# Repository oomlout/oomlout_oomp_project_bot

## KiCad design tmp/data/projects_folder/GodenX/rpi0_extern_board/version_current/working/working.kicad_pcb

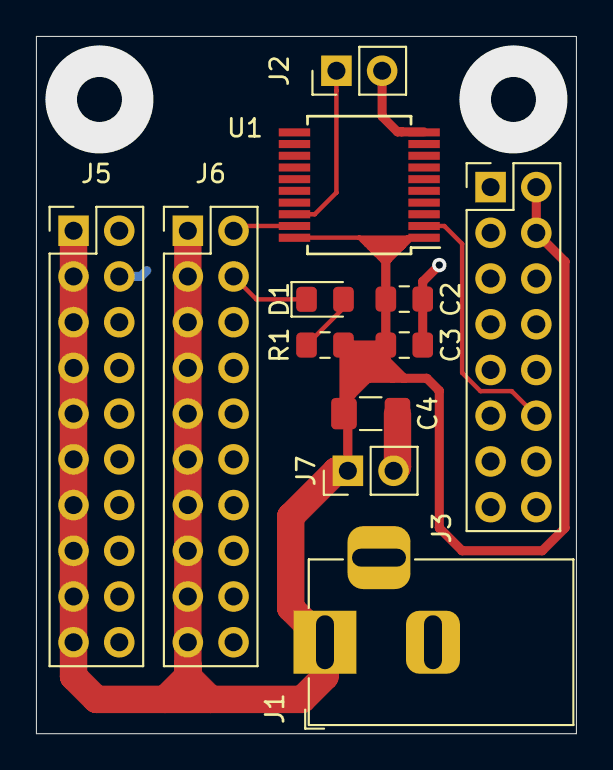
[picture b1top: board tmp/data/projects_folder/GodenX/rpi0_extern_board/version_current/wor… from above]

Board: 2 copper layers, 30.0 x 38.7 mm, 12 parts (0 on the bottom side), 5 nets.

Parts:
C2: 10uF; C_0805_2012Metric_Pad1.15x1.40mm_HandSolder
C3: 0.1uF; C_0805_2012Metric_Pad1.15x1.40mm_HandSolder
C4: 47uF; C_1206_3216Metric_Pad1.42x1.75mm_HandSolder
D1: LED; LED_0805_2012Metric_Pad1.15x1.40mm_HandSolder
J1: Conn_02x08_Odd_Even; PinHeader_2x08_P2.54mm_Vertical
J2, J7: Conn_01x02; PinHeader_1x02_P2.54mm_Vertical
J3: Jack-DC; BarrelJack_Horizontal
J5, J6: Conn_02x10_Odd_Even; PinHeader_2x10_P2.54mm_Vertical
R1: 10K; R_0805_2012Metric_Pad1.15x1.40mm_HandSolder
U1: 74HC245; SSOP-20_5.3x7.2mm_P0.65mm

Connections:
0: C2.2, C3.2, C4.2, D1.1, J1.6, J1.9, J1.14, J2.2, J3.2, J5.2, J5.4, J5.6, J5.8, J5.10, J5.12, J5.14, J5.16, J5.18, J5.20, J6.2, J6.4, J6.6, J6.8, J6.10, J6.12, J6.14, J6.16, J6.18, J6.20, J7.2, U1.10, U1.19
+5V: C2.1, C3.1, C4.1, J1.2, J1.4, J3.1, J5.1, J5.3, J5.5, J5.7, J5.9, J5.11, J5.13, J5.15, J5.17, J5.19, J6.1, J6.3, J6.5, J6.7, J6.9, J6.11, J6.13, J6.15, J6.17, J6.19, J7.1, R1.1, U1.1, U1.20
/Data: J1.12, U1.2
unnamed: D1.2, R1.2
unnamed: J2.1, U1.18

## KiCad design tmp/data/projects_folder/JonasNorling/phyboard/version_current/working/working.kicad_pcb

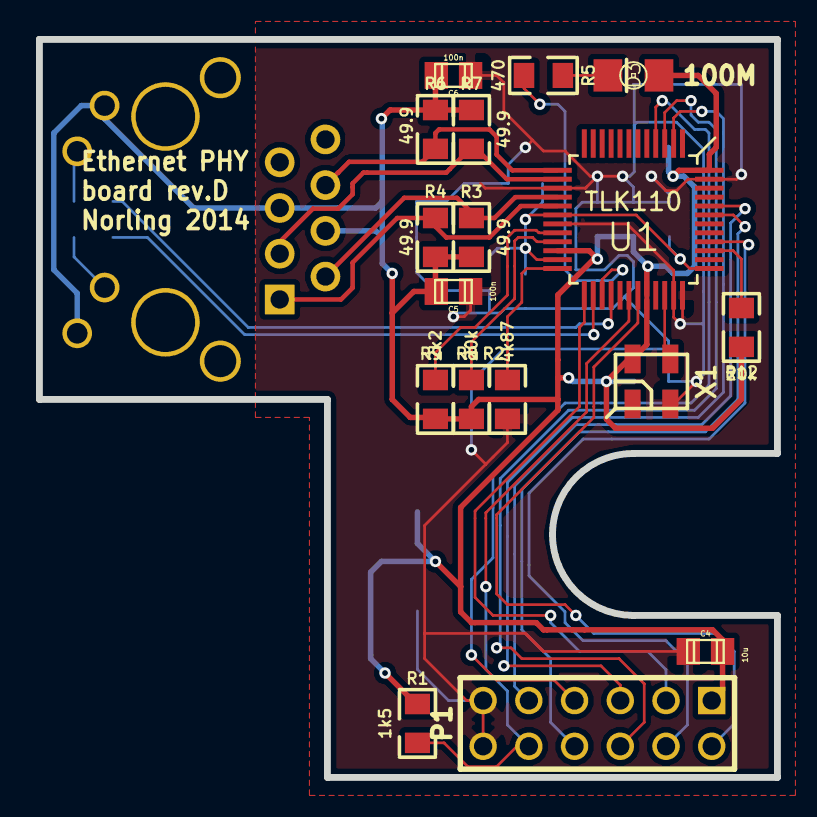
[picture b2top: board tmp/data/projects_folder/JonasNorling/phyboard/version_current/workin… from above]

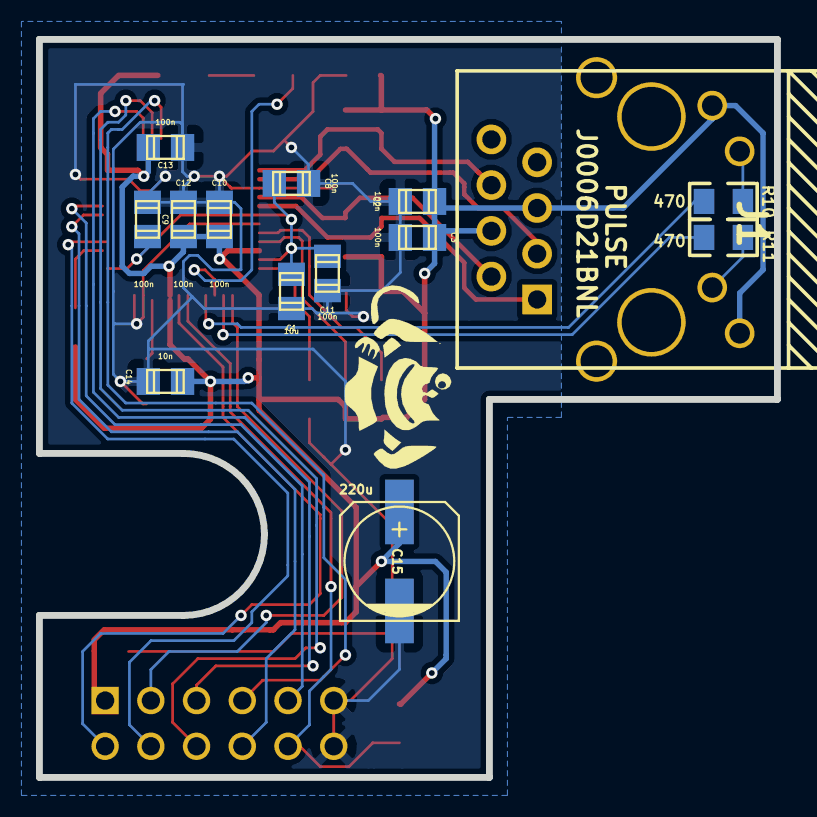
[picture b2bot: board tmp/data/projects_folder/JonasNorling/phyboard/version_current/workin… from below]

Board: 2 copper layers, 41.0 x 41.0 mm, 31 parts (14 on the bottom side), 27 nets.

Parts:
C1, C4: 10u; c_0805
C2, C3, C5, C6, C8, C9, C10, C11, C12, C13: 100n; c_0805
C14: 10n; c_0805
C15: 220u; c_elec_6.3x5.3
D3: LED; LED-1206
J1: PULSE-J0006; pulse-J0006D21BNL
P1: CONN_6X2; pin_array_6x2
R1: 1k5; SM0805-jonas
R2: 4k87; SM0805-jonas
R3, R4, R6, R7: 49.9; SM0805-jonas
R5, R10, R11: 470; SM0805-jonas
R8, R12: 20k; SM0805-jonas
R9: 2k2; SM0805-jonas
U1: TLK110; QFP50P900X900-48M
X1: ASEMB-50.000MHZ-LC-T; oscillator-3.2x2.5

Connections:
+3.3V: C2.1, C3.1, C4.1, C5.1, C6.1, C10.1, C12.1, C13.1, C14.1, C15.1, D3.1, J1.4, J1.5, J1.9, J1.12, P1.1, R1.2, R3.1, R4.2, R6.1, R7.2, R8.2, R9.2, R12.2, U1.22, U1.32, U1.48, X1.4
/ETH_CLK: P1.3, U1.25
/ETH_CRS: P1.4, U1.40
/ETH_MDC: P1.2, U1.31
/ETH_MDIO: P1.10, R1.1, U1.30
/ETH_RxD0: P1.8, U1.43
/ETH_RxD1: P1.9, U1.44
/ETH_TX_EN: P1.5, U1.2
/ETH_TxD0: P1.6, U1.3
/ETH_TxD1: P1.7, U1.4
/LED1: J1.11, R10.2
/LED2: J1.10, R11.2
/LED3: D3.2, R5.2
/OSC: U1.34, X1.3
/PFB: C1.1, C8.1, C9.1, C11.1, U1.18, U1.23, U1.37
/RD+: J1.3, R7.1, U1.14
/RD-: J1.6, R6.2, U1.13
/RMII_MODE: R12.1, U1.39
/TD+: J1.1, R4.1, U1.17
/TD-: J1.2, R3.2, U1.16
GND: C1.2, C2.2, C3.2, C4.2, C5.2, C6.2, C8.2, C9.2, C10.2, C11.2, C12.2, C13.2, C14.2, C15.2, P1.11, P1.12, R2.2, U1.15, U1.19, U1.35, U1.36, U1.47, X1.2
unnamed: R2.1, U1.24
unnamed: R8.1, U1.21
unnamed: R9.1, U1.20
unnamed: R10.1, U1.28
unnamed: R5.1, U1.27
unnamed: R11.1, U1.26

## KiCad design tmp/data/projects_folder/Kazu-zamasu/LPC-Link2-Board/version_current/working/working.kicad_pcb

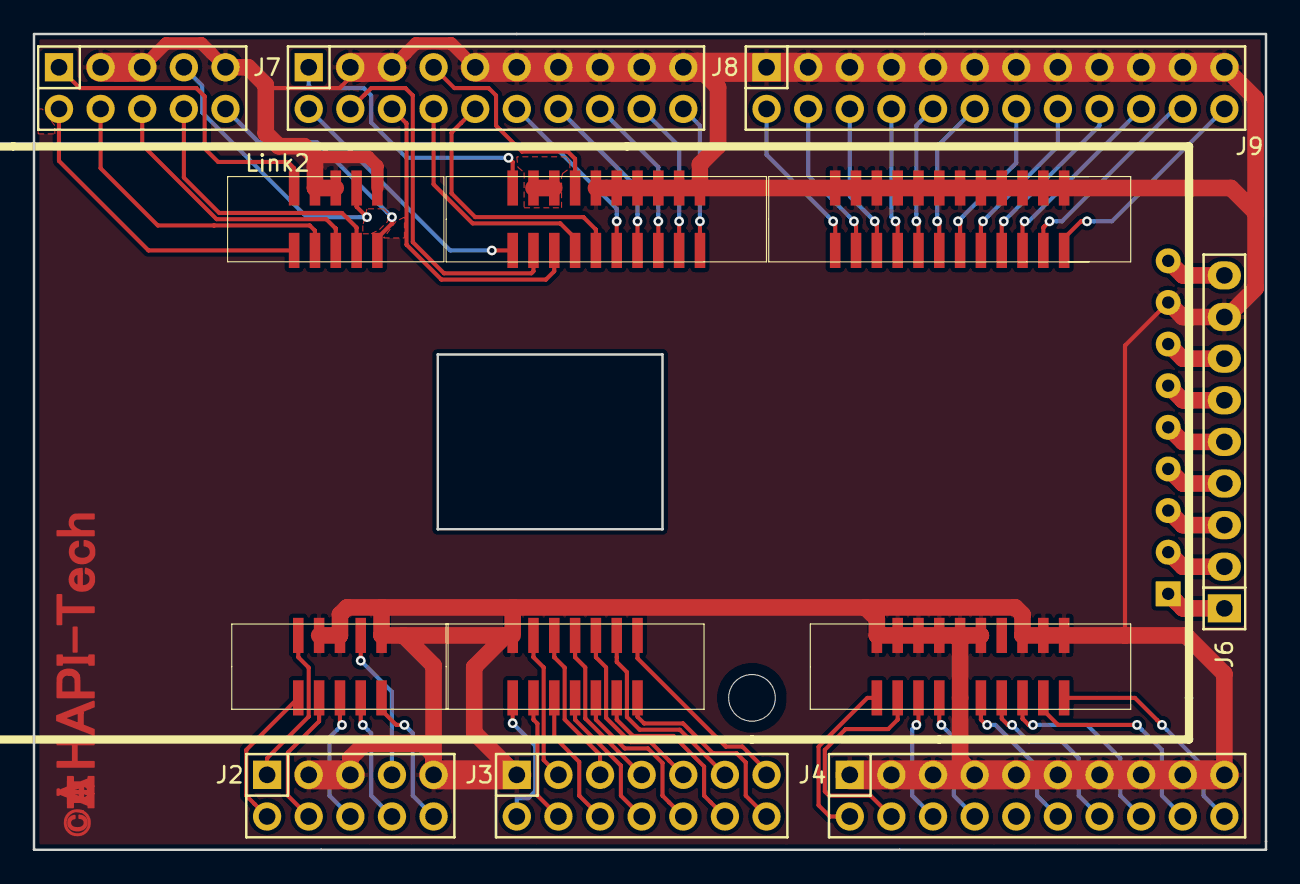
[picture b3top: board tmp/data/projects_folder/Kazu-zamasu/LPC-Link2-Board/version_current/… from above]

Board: 2 copper layers, 75.2 x 49.8 mm, 8 parts (0 on the bottom side), 69 nets.

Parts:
J2, J7: CONN_02X05; Socket_Strip_Straight_2x05
J3: CONN_02X07; Socket_Strip_Straight_2x07
J4, J8: CONN_02X10; Socket_Strip_Straight_2x10
J6: CONN_01X09; Socket_Strip_Straight_1x09
J9: CONN_02X12; Socket_Strip_Straight_2x12
Link2: LPCLink2; LPCLink2_Base-SMT

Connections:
GND: J2.3, J2.5, J2.9, J3.1, J4.1, J4.3, J4.5, J4.7, J4.9, J4.11, J4.13, J4.15, J4.17, J4.19, J6.8, J7.3, J7.5, J7.9, J8.3, J8.5, J8.9, J8.11, J8.13, J8.15, J8.17, J8.19, J9.1, J9.3, J9.5, J9.7, J9.9, J9.11, J9.13, J9.15, J9.17, J9.19, J9.21, J9.23, Link2.2-3, Link2.2-5, Link2.2-9, Link2.3-1, Link2.4-1, Link2.4-3, Link2.4-5, Link2.4-7, Link2.4-9, Link2.4-10, Link2.4-11, Link2.4-15, Link2.4-17, Link2.4-19, Link2.6-8, Link2.7-3, Link2.7-5, Link2.7-9, Link2.8-3, Link2.8-5, Link2.8-9, Link2.8-11, Link2.8-13, Link2.8-15, Link2.8-17, Link2.8-19, Link2.9-1, Link2.9-3, Link2.9-5, Link2.9-7, Link2.9-9, Link2.9-11, Link2.9-13, Link2.9-15, Link2.9-17, Link2.9-19, Link2.9-21, Link2.9-23
unnamed: J2.1, Link2.2-1
unnamed: J2.2, Link2.2-2
unnamed: J2.4, Link2.2-4
unnamed: J2.6, Link2.2-6
unnamed: J2.7, Link2.2-7
unnamed: J2.8, Link2.2-8
unnamed: J2.10, Link2.2-10
unnamed: J3.2, Link2.3-2
unnamed: J3.3, Link2.3-3
unnamed: J3.4, Link2.3-4
unnamed: J3.5, Link2.3-5
unnamed: J3.6, Link2.3-6
unnamed: J3.7, Link2.3-7
unnamed: J3.8, Link2.3-8
unnamed: J3.9, Link2.3-9
unnamed: J3.10, Link2.3-10
unnamed: J3.11, Link2.3-11
unnamed: J3.12, Link2.3-12
unnamed: J3.13, Link2.3-13
unnamed: J3.14, Link2.3-14
unnamed: J4.2, Link2.4-2
unnamed: J4.4, Link2.4-4
unnamed: J4.6, Link2.4-6
unnamed: J4.8, Link2.4-8
unnamed: J4.12, Link2.4-12
unnamed: J4.14, Link2.4-14
unnamed: J4.16, Link2.4-16
unnamed: J4.18, Link2.4-18
unnamed: J4.20, Link2.4-20
unnamed: J6.1, Link2.6-1
unnamed: J6.2, Link2.6-2
unnamed: J6.3, Link2.6-3
unnamed: J6.4, Link2.6-4
unnamed: J6.5, Link2.6-5
unnamed: J6.6, Link2.6-6
unnamed: J6.7, Link2.6-7
unnamed: J6.9, Link2.6-9
unnamed: J7.1, Link2.7-1
unnamed: J7.2, Link2.7-2
unnamed: J7.4, Link2.7-4
unnamed: J7.6, Link2.7-6
unnamed: J7.7, Link2.7-7
unnamed: J7.8, Link2.7-8
unnamed: J7.10, Link2.7-10
unnamed: J8.1, Link2.8-1
unnamed: J8.2, Link2.8-2
unnamed: J8.4, Link2.8-4
unnamed: J8.6, Link2.8-6
unnamed: J8.7, Link2.8-7
unnamed: J8.8, Link2.8-8
unnamed: J8.10, Link2.8-10
unnamed: J8.12, Link2.8-12
unnamed: J8.14, Link2.8-14
unnamed: J8.16, Link2.8-16
unnamed: J8.18, Link2.8-18
unnamed: J8.20, Link2.8-20
unnamed: J9.2, Link2.9-2
unnamed: J9.4, Link2.9-4
unnamed: J9.6, Link2.9-6
unnamed: J9.8, Link2.9-8
unnamed: J9.10, Link2.9-10
unnamed: J9.12, Link2.9-12
unnamed: J9.14, Link2.9-14
unnamed: J9.16, Link2.9-16
unnamed: J9.18, Link2.9-18
unnamed: J9.20, Link2.9-20
unnamed: J9.22, Link2.9-22
unnamed: J9.24, Link2.9-24

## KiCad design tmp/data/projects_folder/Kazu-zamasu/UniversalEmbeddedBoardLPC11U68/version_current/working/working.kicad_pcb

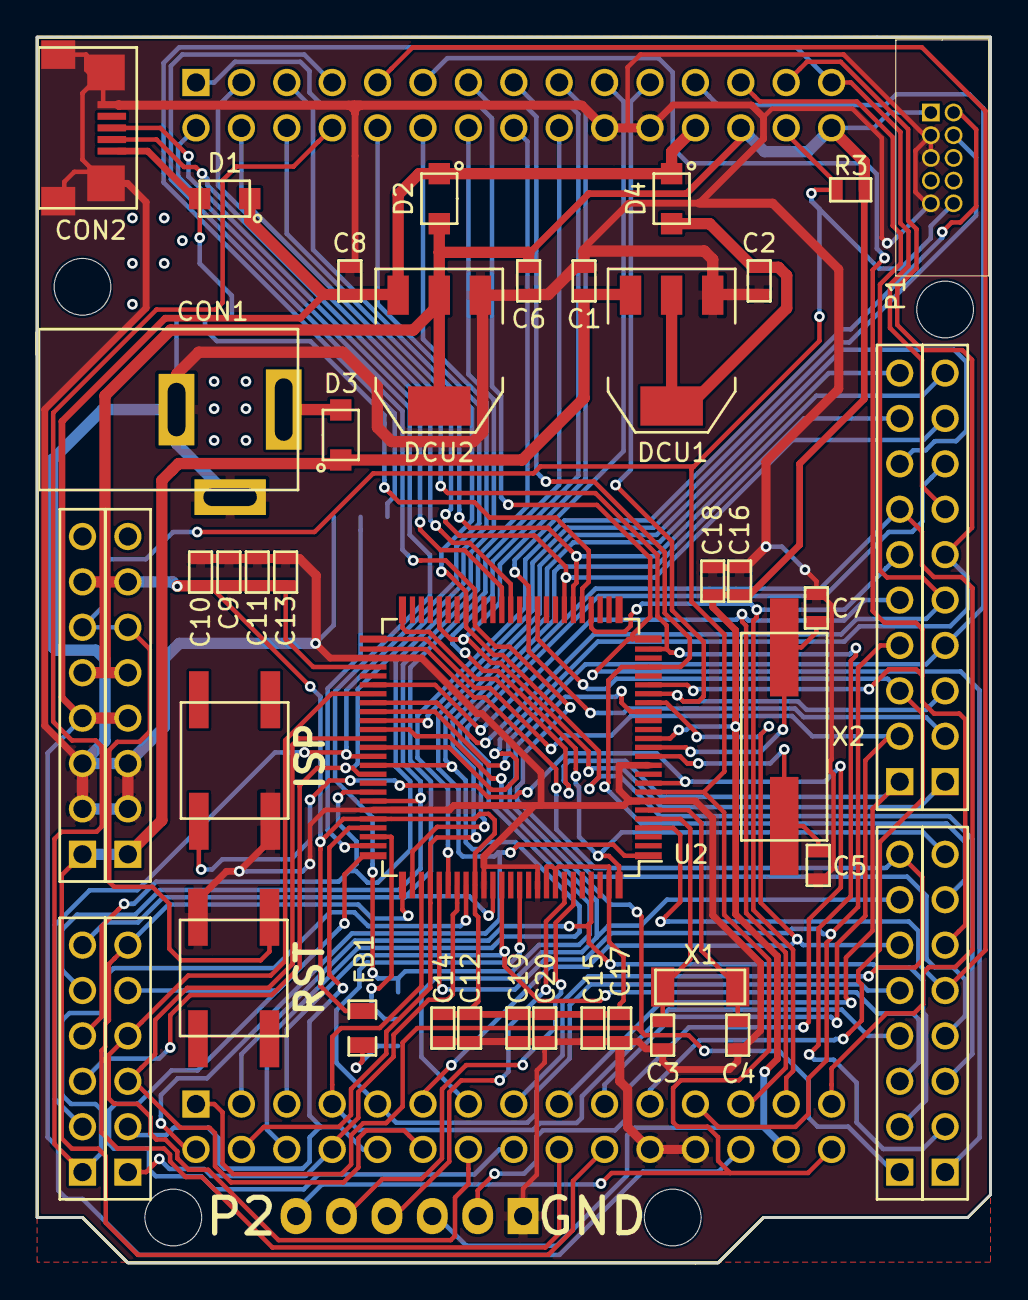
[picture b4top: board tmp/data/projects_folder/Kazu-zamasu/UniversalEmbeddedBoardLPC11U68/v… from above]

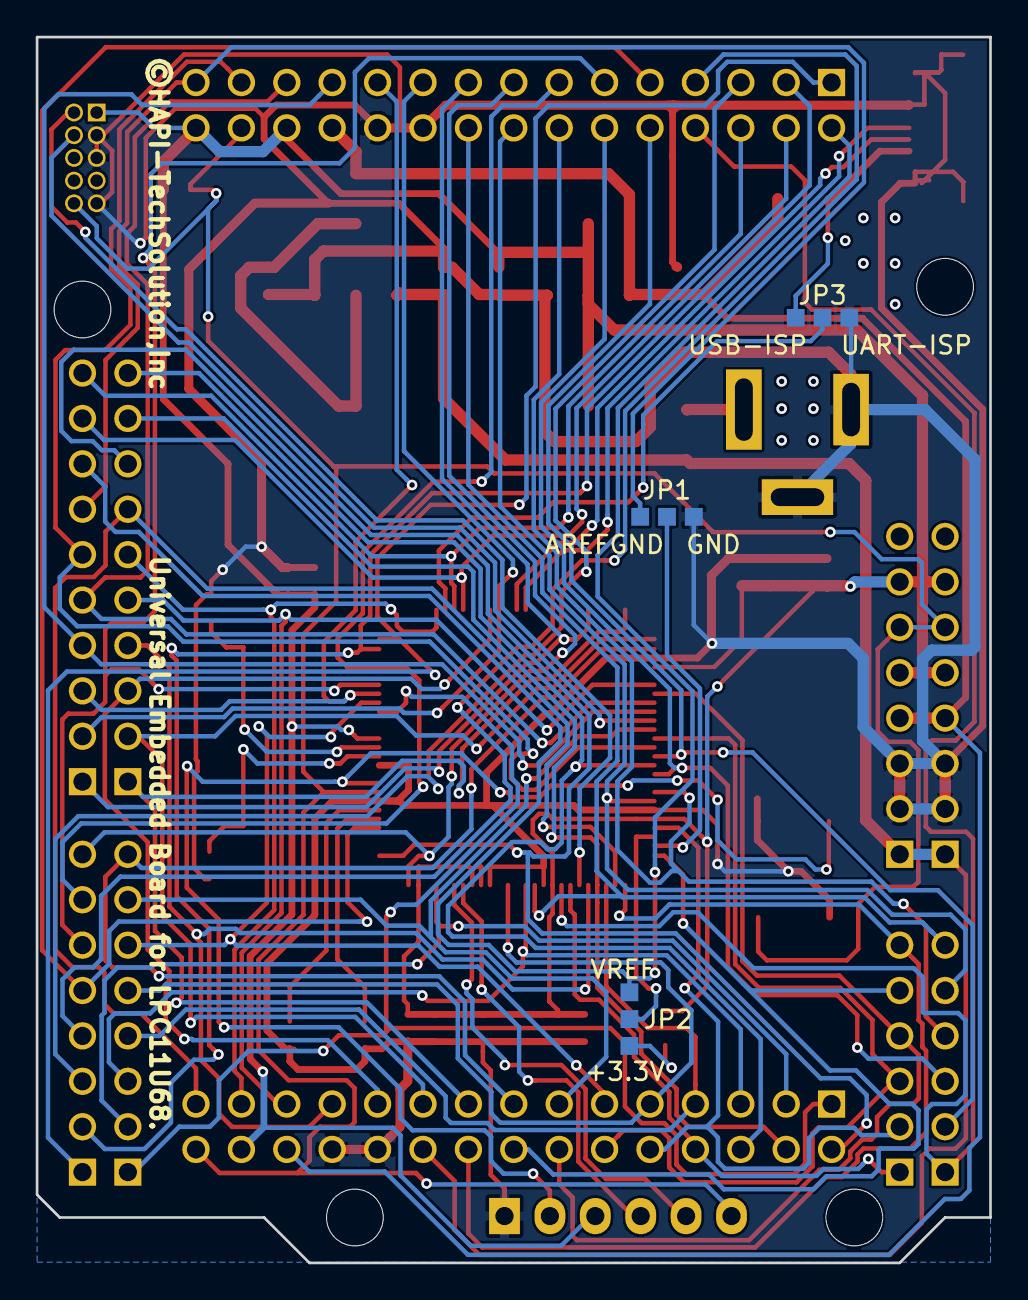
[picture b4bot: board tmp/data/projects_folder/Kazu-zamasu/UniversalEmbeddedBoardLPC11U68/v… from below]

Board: 2 copper layers, 53.3 x 68.6 mm, 42 parts (5 on the bottom side), 71 nets.

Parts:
C1, C2, C6, C8, C17: 1uF; SMD-0603
C3, C4: 18pF; SMD-0603
C5, C7: 27pF; SMD-0603
C9, C11, C12, C15, C18, C19: 0.1uF; SMD-0603
C10, C13, C14, C16, C20: 0.01uF; SMD-0603
CON1: MJ-179P; DCJack_MJ-179P
CON2: HIROSE ZX62R-B-5P; Hirose-microUSB-ZX62R-B-5P
D1, D2, D3, D4: PMEG2010ER,115
DCU1: AZ1117E-5.0V; SOT-223
DCU2: AZ1117E-3.3V; SOT-223
FB1: R; SMD-0805
JP1, JP2, JP3: JUMPER3; SJ-3Pin
OPT1: Arduino-Shiled2(11x)Inside; Arduino-Shield-Inside-Outline
OPT2: Arduino-Shiled; Arduino-Shield-Normal-Outline
P1: CONN_02X05; JTAG-Half-2x5
P2: CONN_01X06; Pin_Header_Angled_1x06
R3: 100k; SMD-0603
SW1, SW2: SW_PUSH; SW_TACT-EVQQ2Y03W
U2: LPC11U68JBD100; LPC11E68-TQFP-100
X1: 32.768KHZ; FC-255-RTC-Xtal
X2: 12MHz; HC-49_S

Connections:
+3V3: C6.1, C9.1, C10.1, C11.1, C12.1, C13.1, C14.1, C15.1, C16.1, C17.1, C18.2, C19.1, C20.1, D2.1, DCU2.2, DCU2.4, FB1.1, OPT1.28, OPT1.30, OPT2.28, OPT2.30, P1.1, P2.3, R3.2, U2.14, U2.54, U2.71, U2.84, U2.92, U2.93, U2.99
+5V: C8.1, D1.2, D2.2, D4.2, DCU2.3, OPT1.27, OPT2.27
AREFGND: JP1.3, OPT2.14
GND: C1.1, C2.1, C3.2, C4.1, C5.2, C6.2, C7.1, C8.2, C9.2, C10.2, C11.2, C12.2, C13.2, C14.2, C15.2, C16.2, C17.2, C18.1, C19.2, C20.2, CON1.2, CON1.3, CON2.5, CON2.6, CON2.7, CON2.8, CON2.9, DCU1.1, DCU2.1, JP1.1, JP3.3, OPT1.25, OPT1.26, OPT2.25, OPT2.26, P1.3, P1.5, P1.9, P2.1, SW1.2, SW2.2, U2.7, U2.11, U2.53, U2.70, U2.85, U2.91
ISP: P2.2, SW2.1, U2.9
unnamed: C2.2, D4.1, DCU1.2, DCU1.4
unnamed: C3.1, U2.5, X1.1
unnamed: C4.2, U2.6, X1.2
unnamed: C5.1, U2.12, X2.1
unnamed: C7.2, U2.13, X2.2
unnamed: CON1.1, D3.1
unnamed: FB1.2, JP2.1
unnamed: JP1.2, U2.74
unnamed: JP2.2, U2.73
PIO0_2: OPT2.10, U2.19
PIO0_3(USB_VBUS): JP3.2, U2.30
PIO0_4: OPT2.17, U2.31
PIO0_5: OPT2.16, U2.32
PIO0_8: OPT2.12, U2.58
PIO0_9: OPT2.11, U2.59
PIO0_11: OPT2.19, U2.64
PIO0_12: OPT2.20, U2.66
PIO0_13: OPT2.21, U2.68
PIO0_14: OPT2.22, U2.69
PIO0_16: OPT1.18, U2.82
PIO0_18: P2.4, U2.94
PIO0_19: P2.5, U2.95
PIO0_20: OPT1.0, U2.17
PIO0_22: OPT1.20, U2.62
PIO0_23: OPT2.18, U2.83
PIO1_0: OPT1.1, U2.97
PIO1_3: OPT1.19, U2.72
PIO1_8: OPT1.6, U2.61
PIO1_9: OPT2.23, U2.86
PIO1_10: OPT1.5, U2.18
PIO1_11: OPT1.17, U2.65
PIO1_12: OPT1.4, U2.89
PIO1_13: OPT1.3, U2.78
PIO1_14: OPT1.16, U2.79
PIO1_15: OPT1.2, U2.87
PIO1_18: OPT2.2, U2.43
PIO1_19: OPT2.4, U2.4
PIO1_20: OPT1.13, U2.29
PIO1_21: OPT1.12, U2.56
PIO1_22: OPT1.11, U2.80
PIO1_23: OPT1.10, U2.35
PIO1_24: OPT2.3, U2.42
PIO1_25: OPT2.7, U2.100
PIO1_26: OPT2.5, U2.20
PIO1_27: OPT2.6, U2.22
PIO1_28: OPT2.8, U2.46
PIO1_29: OPT2.13, U2.63
PIO2_3: OPT2.9, U2.36
PIO2_11: OPT2.0, U2.25
PIO2_12: OPT2.1, U2.24
PIO2_16: OPT1.8, U2.50
PIO2_17: OPT1.9, U2.51
PIO2_18: OPT1.7, U2.52
PIO2_19: OPT1.21, U2.57
PIO2_20: OPT1.22, U2.75
PIO2_21: OPT1.23, U2.76
PIO2_22: OPT1.14, U2.77
PIO2_23: OPT1.15, U2.1
RESETn: OPT1.29, OPT2.29, P1.10, P2.6, R3.1, SW1.1, U2.8
SWCLK: P1.4, U2.60
SWDIO: P1.2, U2.81
USB-VDD: CON2.1, D1.1, JP3.1
USB_DM: CON2.2, U2.38
USB_DP: CON2.3, U2.39
VREF: JP2.3, OPT2.15
Vin: C1.2, D3.2, DCU1.3, OPT1.24, OPT2.24

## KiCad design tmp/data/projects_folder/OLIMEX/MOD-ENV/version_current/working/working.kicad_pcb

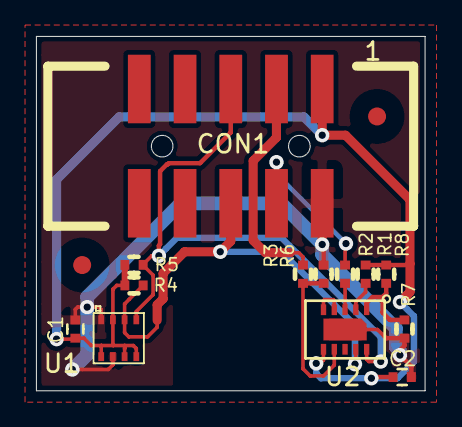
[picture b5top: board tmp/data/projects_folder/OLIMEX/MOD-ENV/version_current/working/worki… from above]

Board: 2 copper layers, 21.6 x 19.7 mm, 15 parts (0 on the bottom side), 11 nets.

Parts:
C1, C2: 100nF; C_0402_5MIL_DWS
CON1: BH10S; UEXTM-SMD
R1, R4, R5: 4.7K; R_0402_5MIL_DWS
R2, R3: (n.a.)100R; R_0402_5MIL_DWS
R6, R7: 100R; R_0402_5MIL_DWS
R8: (N.A.)100R; R_0402_5MIL_DWS
Ref*: Val**; Fiducial1x3_transp
Ref*#2: Val**; Fiducial1x3_transp
U1: BME280
U2: CCS811

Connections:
GND: C1.2, C2.2, CON1.2, R6.2, R7.1, U1.1, U1.7, U2.EP
unnamed: CON1.3, R3.2
unnamed: CON1.4, R2.2
unnamed: CON1.5, R5.1, U1.4, U2.10
unnamed: CON1.6, R4.1, U1.3, U2.9
unnamed: R1.1, U2.2
unnamed: R2.1, U2.3
unnamed: R3.1, R6.1, U2.7
unnamed: R7.2, R8.2, U2.1
unnamed: U2.4, U2.5
VDD: C1.1, C2.1, CON1.1, R1.2, R4.2, R5.2, R8.1, U1.2, U1.5, U1.6, U1.8, U2.6

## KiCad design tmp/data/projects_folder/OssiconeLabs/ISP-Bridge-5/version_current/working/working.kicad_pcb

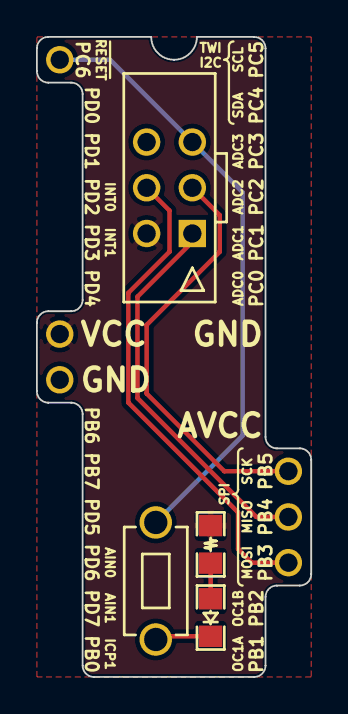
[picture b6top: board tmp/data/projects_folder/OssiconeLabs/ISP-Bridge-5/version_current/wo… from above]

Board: 2 copper layers, 15.2 x 35.6 mm, 6 parts (0 on the bottom side), 7 nets.

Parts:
D1: LED; LED_0805_Symbol
IC1: ATMEGA328-P; Atmel_ATtiny-x8_ATmega-x8
J1: ATMEL_ISP_6PIN; Atmel_ISP_6PIN
R1: 1K; R_0805_Symbol
SW1: SW_PUSH; SW_PUSH_MJTP1250
VAL: REF; Ossicone_Labs_Logo_0.165prop_flipped

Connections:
GND: D1.1, IC1.8, J1.6, SW1.1
unnamed: D1.2, R1.2
unnamed: IC1.1, J1.5, SW1.2
unnamed: IC1.17, J1.4
unnamed: IC1.18, J1.1
unnamed: IC1.19, J1.3
VCC: IC1.7, J1.2, R1.1

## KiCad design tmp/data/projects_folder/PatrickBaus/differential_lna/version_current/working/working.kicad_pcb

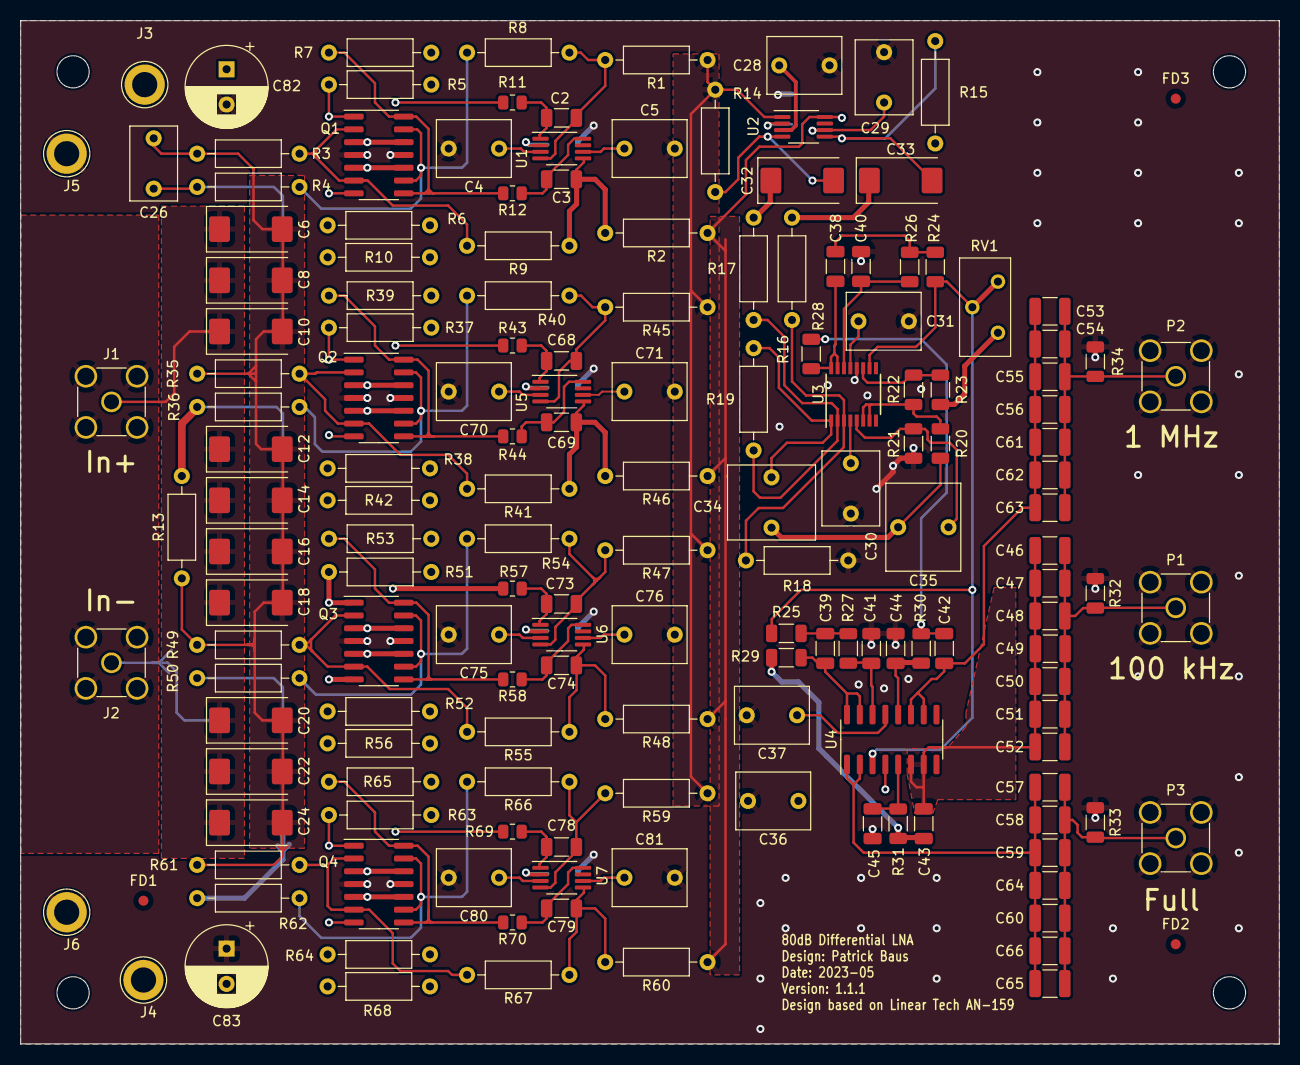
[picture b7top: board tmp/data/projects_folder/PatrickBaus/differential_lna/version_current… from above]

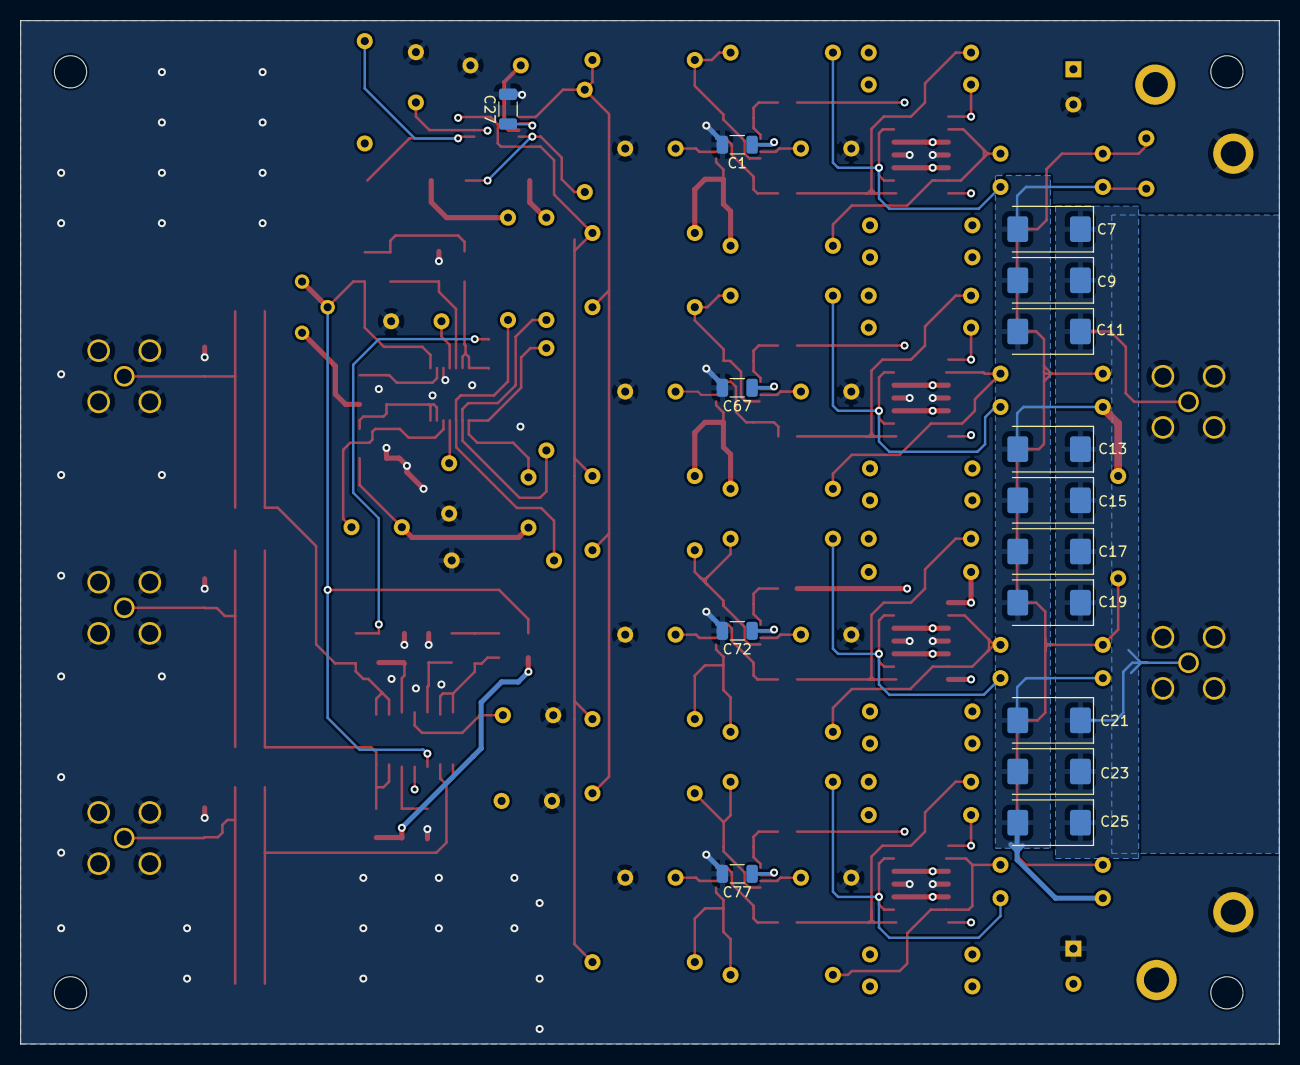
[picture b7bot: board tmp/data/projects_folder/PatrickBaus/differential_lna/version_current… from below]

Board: 4 copper layers, 125.0 x 101.6 mm, 181 parts (15 on the bottom side), 84 nets.

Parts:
C1, C27, C67, C72, C77: 1u; C_1206_3216Metric
C2, C3, C68, C69, C73, C74, C78, C79: 33p; C_1206_3216Metric
C4, C5, C28, C29, C30, C31, C36, C37, C70, C71, C75, C76, C80, C81: 1u; C_Rect_L7.2mm_W5.5mm_P5.00mm_FKS2_FKP2_MKS2_MKP2
C6, C7, C8, C9, C10, C11, C12, C13, C14, C15, C16, C17, C18, C19, C20, C21, C22, C23, C24, C25: 150u; CP_EIA-7343-43_Kemet-X
C26: 2.2n; C_Rect_L7.2mm_W4.5mm_P5.00mm_FKS2_FKP2_MKS2_MKP2
C32, C33: 330u; CP_EIA-7343-31_Kemet-D
C34, C35: 4.7u; C_Rect_L7.2mm_W8.5mm_P5.00mm_FKP2_FKP2_MKS2_MKP2
C38: 120p; C_1206_3216Metric
C39: 1.2n; C_1206_3216Metric
C40: 100p; C_1206_3216Metric
C41: 1n; C_1206_3216Metric
C42: 150p; C_1206_3216Metric
C43: 1.5n; C_1206_3216Metric
C44: 22p; C_1206_3216Metric
C45: 220p; C_1206_3216Metric
C46, C47, C48, C49, C50, C51, C52, C53, C54, C55, C56, C57, C58, C59, C60, C61, C62, C63, C64, C65, C66: 100u; C_1210_3225Metric
C82, C83: 180u; CP_Radial_D8.0mm_P3.50mm
FD1, FD2, FD3: FIDUCIAL; Fiducial_1mm_Mask2mm
H1, H2, H3, H4: MountingHole; MountingHole_3.2mm_M3_DIN965
J1, J2: SMA; SMA_Amphenol_901-144_Vertical
J3, J4, J5, J6: CONN_01X01; TestPoint_Loop_D3.80mm_Drill2.5mm
P1, P2, P3: SMA; SMA_Amphenol_901-144_Vertical
Q1, Q2, Q3, Q4: THAT300; SOIC-14_3.9x8.7mm_P1.27mm
R1, R2, R45, R46, R47, R48, R59, R60: 100; R_Axial_DIN0207_L6.3mm_D2.5mm_P10.16mm_Horizontal
R3, R4, R35, R36, R49, R50, R61, R62: 49.9; R_Axial_DIN0207_L6.3mm_D2.5mm_P10.16mm_Horizontal
R5, R6, R7, R10, R37, R38, R39, R42, R51, R52, R53, R56, R63, R64, R65, R68: 4.02k; R_Axial_DIN0207_L6.3mm_D2.5mm_P10.16mm_Horizontal
R8, R9, R40, R41, R54, R55, R66, R67: 1.3k; R_Axial_DIN0207_L6.3mm_D2.5mm_P10.16mm_Horizontal
R11, R12, R43, R44, R57, R58, R69, R70: 1k; R_0805_2012Metric
R13, R18, R19: 1k; R_Axial_DIN0207_L6.3mm_D2.5mm_P10.16mm_Horizontal
R14, R15: 249; R_Axial_DIN0207_L6.3mm_D2.5mm_P10.16mm_Horizontal
R16, R17: 475; R_Axial_DIN0207_L6.3mm_D2.5mm_P10.16mm_Horizontal
R20: 2k; R_1206_3216Metric
R21: 5.76k; R_1206_3216Metric
R22: 100; R_1206_3216Metric
R23: 1.5k; R_1206_3216Metric
R24, R25: 1.69k; R_1206_3216Metric
R26, R27: 1.24k; R_1206_3216Metric
R28, R29: 4.02k; R_1206_3216Metric
R30, R31: 2.15k; R_1206_3216Metric
R32, R33, R34: 49.9; R_1206_3216Metric
RV1: 1k; Potentiometer_Bourns_3296Y_Vertical
U1, U2, U5, U6, U7: LT1994; MSOP-8_3x3mm_P0.65mm
U3: LT6232; SSOP-16_3.9x4.9mm_P0.635mm
U4: LT1365; SOIC-16_3.9x9.9mm_P1.27mm

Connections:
/2nd stage differential/IN+: R1.1, R14.2, R45.1, R47.1, R59.1, U2.1
/2nd stage differential/IN-: R2.1, R15.2, R46.1, R48.1, R60.1, U2.8
/2nd stage differential/OUT+: C33.2, R15.1, U2.5
/2nd stage differential/OUT-: C32.2, R14.1, U2.4
/2nd stage differential/V+: C4.1, C28.1, C30.1, C36.1, C70.1, C75.1, C80.1, C82.1, J3.1, R5.1, R7.1, R37.1, R39.1, R51.1, R53.1, R63.1, R65.1, U1.3, U2.3, U3.4 (V+), U4.4 (V+), U5.3, U6.3, U7.3
/2nd stage differential/V-: C5.1, C29.1, C31.1, C37.1, C71.1, C76.1, C81.1, C83.2, J4.1, R6.2, R10.2, R38.2, R42.2, R52.2, R56.2, R64.2, R68.2, U1.6, U2.6, U3.13 (V-), U4.13 (V-), U5.6, U6.6, U7.6
/Differential to single ended/OUT: R20.2, R22.2, U3.6 (-), U3.7
/Final amplifier stage/OUT: R24.2, R25.2, RV1.2, RV1.3, U3.10, U4.3 (+)
/Input Filter/In+: C6.1, C8.1, C10.1, C12.1, C14.1, C16.1, C18.1, C20.1, C22.1, C24.1, J1.1 (In)
/Input Filter/In-: C7.1, C9.1, C11.1, C13.1, C15.1, C17.1, C19.1, C21.1, C23.1, C25.1, J2.1 (In)
/Input Filter/Out+: C6.2, C8.2, C10.2, C12.2, C14.2, C16.2, C18.2, C20.2, C22.2, C24.2, C26.1, R3.2, R13.1, R35.2, R49.2, R61.2
/Input Filter/Out-: C7.2, C9.2, C11.2, C13.2, C15.2, C17.2, C19.2, C21.2, C23.2, C25.2, C26.2, R4.2, R13.2, R36.2, R50.2, R62.2
/Output/OUT: C57.1, C58.1, C59.1, C60.1, C64.1, C65.1, C66.1, P3.1 (In), R33.2
/Output/OUT_1MHz: C53.1, C54.1, C55.1, C56.1, C61.1, C62.1, C63.1, P2.1 (In), R34.2
/Output/OUT_100kHz: C46.1, C47.1, C48.1, C49.1, C50.1, C51.1, C52.1, P1.1 (In), R32.2
/Preamplifier 2/OUT+: C68.1, R40.1, R45.2, U5.4
/Preamplifier 2/OUT-: C69.1, R41.1, R46.2, U5.5
/Preamplifier 3/OUT+: C73.1, R47.2, R54.1, U6.4
/Preamplifier 3/OUT-: C74.1, R48.2, R55.1, U6.5
/Preamplifier 4/OUT+: C78.1, R59.2, R66.1, U7.4
/Preamplifier 4/OUT-: C79.1, R60.2, R67.1, U7.5
/Preamplifier/OUT+: C2.1, R1.2, R8.1, U1.4
/Preamplifier/OUT-: C3.1, R2.2, R9.1, U1.5
GND: C1.2, C4.2, C5.2, C27.2, C28.2, C29.2, C30.2, C31.2, C36.2, C37.2, C40.2, C41.2, C44.2, C45.2, C67.2, C70.2, C71.2, C72.2, C75.2, C76.2, C77.2, C80.2, C81.2, C82.2, C83.1, J5.1, J6.1, P1.2 (Ext), P2.2 (Ext), P3.2 (Ext), Q1.4 (B), Q1.11 (E), Q2.4 (B), Q2.11 (E), Q3.4 (B), Q3.11 (E), Q4.4 (B), Q4.11 (E), R18.2, R21.2, R32.1, R33.1, R34.1, U3.12 (+)
GNDPWR: J1.2 (Ext), J2.2 (Ext)
unnamed: C1.1, U1.2
unnamed: C2.2, R11.1, U1.1
unnamed: C3.2, R12.1, U1.8
unnamed: C27.1, U2.2
unnamed: C32.1, R17.2
unnamed: C33.1, R16.2
unnamed: C34.1, C35.2, R20.1
unnamed: C34.2, R19.2, U3.1
unnamed: C38.2, R24.1, R26.2
unnamed: C39.2, R25.1, R27.2
unnamed: C42.2, R28.1, R30.2
unnamed: C43.2, R29.1, R31.2
unnamed: C67.1, U5.2
unnamed: C68.2, R43.1, U5.1
unnamed: C69.2, R44.1, U5.8
unnamed: C72.1, U6.2
unnamed: C73.2, R57.1, U6.1
unnamed: C74.2, R58.1, U6.8
unnamed: C77.1, U7.2
unnamed: C78.2, R69.1, U7.1
unnamed: C79.2, R70.1, U7.8
unnamed: Q1.2 (B), Q1.6 (B), R3.1, R9.2
unnamed: Q1.1 (C), Q1.7 (C), R5.2, R11.2
unnamed: Q1.3 (E), Q1.12 (E), R6.1
unnamed: Q1.9 (B), Q1.13 (B), R4.1, R8.2
unnamed: Q1.8, Q1.14 (C), R7.2, R12.2
unnamed: Q1.5 (E), Q1.10 (E), R10.1
unnamed: Q2.2 (B), Q2.6 (B), R35.1, R41.2
unnamed: Q2.1 (C), Q2.7 (C), R37.2, R43.2
unnamed: Q2.3 (E), Q2.12 (E), R38.1
unnamed: Q2.9 (B), Q2.13 (B), R36.1, R40.2
unnamed: Q2.8, Q2.14 (C), R39.2, R44.2
unnamed: Q2.5 (E), Q2.10 (E), R42.1
unnamed: Q3.2 (B), Q3.6 (B), R49.1, R55.2
unnamed: Q3.1 (C), Q3.7 (C), R51.2, R57.2
unnamed: Q3.3 (E), Q3.12 (E), R52.1
unnamed: Q3.9 (B), Q3.13 (B), R50.1, R54.2
unnamed: Q3.8, Q3.14 (C), R53.2, R58.2
unnamed: Q3.5 (E), Q3.10 (E), R56.1
unnamed: Q4.2 (B), Q4.6 (B), R61.1, R67.2
unnamed: Q4.1 (C), Q4.7 (C), R63.2, R69.2
unnamed: Q4.3 (E), Q4.12 (E), R64.1
unnamed: Q4.9 (B), Q4.13 (B), R62.1, R66.2
unnamed: Q4.8, Q4.14 (C), R65.2, R70.2
unnamed: Q4.5 (E), Q4.10 (E), R68.1
unnamed: R23.1, RV1.1
unnamed: R16.1, R18.1, U3.3 (+)
unnamed: R17.1, R19.1, U3.2 (-)
unnamed: C35.1, R21.1, U3.5 (+)
unnamed: R22.1, R23.2, U3.11 (-)
unnamed: C40.1, R26.1, U3.14 (+)
unnamed: C38.1, R28.2, U3.15 (-), U3.16
unnamed: C57.2, C58.2, C59.2, C60.2, C64.2, C65.2, C66.2, U4.1, U4.2 (-)
unnamed: C45.1, R31.1, U4.5 (+)
unnamed: C43.1, C46.2, C47.2, C48.2, C49.2, C50.2, C51.2, C52.2, U4.6 (-), U4.7
unnamed: C44.1, R30.1, U4.12 (+)
unnamed: C42.1, C53.2, C54.2, C55.2, C56.2, C61.2, C62.2, C63.2, U4.10, U4.11 (-)
unnamed: C41.1, R27.1, U4.14 (+)
unnamed: C39.1, R29.2, U4.15 (-), U4.16

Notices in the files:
tmp/data/projects_folder/Kazu-zamasu/UniversalEmbeddedBoardLPC11U68/version_current/working/working.kicad_pcb:
©HAPI-TechSolution,Inc
